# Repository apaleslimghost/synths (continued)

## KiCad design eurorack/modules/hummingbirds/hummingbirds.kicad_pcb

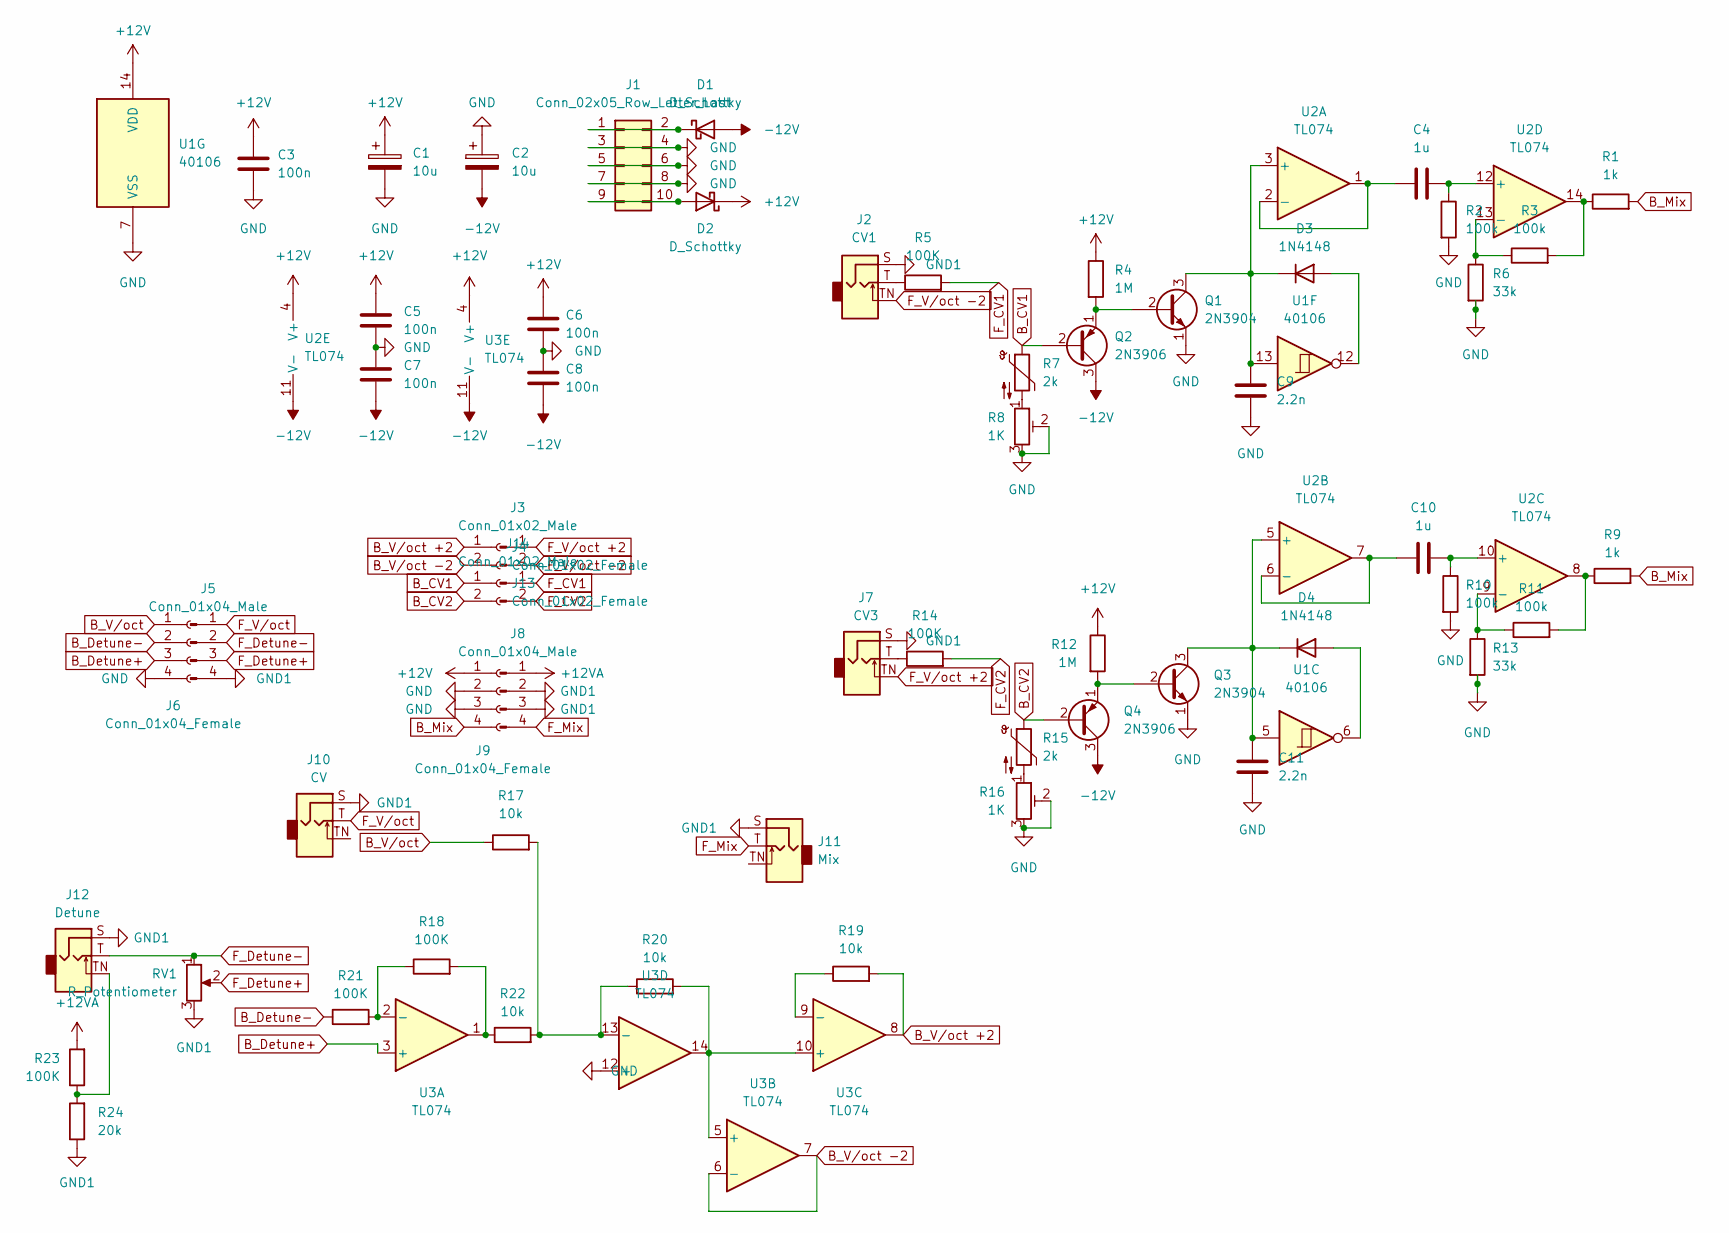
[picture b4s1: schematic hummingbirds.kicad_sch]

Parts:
C1, C2: 10u; CP_Elec_4x5.8
C3, C5, C6, C7, C8: 100n; C_0805_2012Metric_Pad1.18x1.45mm_HandSolder
C4, C10: 1u; C_1210_3225Metric_Pad1.33x2.70mm_HandSolder
C9, C11: 2.2n; C_1206_3216Metric_Pad1.33x1.80mm_HandSolder
D1, D2: D_Schottky; D_SOD-123
D3, D4: 1N4148; D_0805_2012Metric_Pad1.15x1.40mm_HandSolder
J1: Conn_02x05_Row_Letter_Last; PinHeader_2x05_P2.54mm_Vertical_SMD
J2: CV1; Jack_3.5mm_QingPu_WQP-PJ398SM_Vertical
J3, J14: Conn_01x02_Male; PinHeader_1x02_P2.54mm_Vertical
J4, J13: Conn_01x02_Female; PinSocket_1x02_P2.54mm_Vertical
J5, J8: Conn_01x04_Male; PinHeader_1x04_P2.54mm_Vertical
J6, J9: Conn_01x04_Female; PinSocket_1x04_P2.54mm_Vertical
J7: CV3; Jack_3.5mm_QingPu_WQP-PJ398SM_Vertical
J10: CV; Jack_3.5mm_QingPu_WQP-PJ398SM_Vertical
J11: Mix; Jack_3.5mm_QingPu_WQP-PJ398SM_Vertical
J12: Detune; Jack_3.5mm_QingPu_WQP-PJ398SM_Vertical
Q1, Q3: 2N3904; SOT-23_Handsoldering
Q2, Q4: 2N3906; SOT-23_Handsoldering
R1, R9: 1k; R_0805_2012Metric_Pad1.20x1.40mm_HandSolder
R2, R3, R10, R11: 100k; R_0805_2012Metric_Pad1.20x1.40mm_HandSolder
R4, R12: 1M; R_0805_2012Metric_Pad1.20x1.40mm_HandSolder
R5, R14, R18, R21, R23: 100K; R_0805_2012Metric_Pad1.20x1.40mm_HandSolder
R6, R13: 33k; R_0805_2012Metric_Pad1.20x1.40mm_HandSolder
R7, R15: 2k; R_0805_2012Metric_Pad1.20x1.40mm_HandSolder
R8, R16: 1K; Potentiometer_Bourns_3296X_Horizontal
R17, R19, R20, R22: 10k; R_0805_2012Metric_Pad1.20x1.40mm_HandSolder
R24: 20k; R_0805_2012Metric_Pad1.20x1.40mm_HandSolder
RV1: R_Potentiometer; Potentiometer_Alpha_RD901F-40-00D_Single_Vertical
U1: 40106; SOIC-14_3.9x8.7mm_P1.27mm
U2, U3: TL074; SOIC-14_3.9x8.7mm_P1.27mm

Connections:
+12V: C1.1, C3.2, C5.2, C6.2, D2.1 (K), J9.1, R4.1, R12.1, U1.14 (VDD), U2.4 (V+), U3.4 (V+)
+12VA: J8.1, R23.2
-12V: C2.2, C7.1, C8.1, D1.2 (A), Q2.3 (C), Q4.3 (C), U2.11 (V-), U3.11 (V-)
B_CV1: J13.1, Q2.2 (B), R7.1
B_CV2: J13.2, Q4.2 (B), R15.1
B_Detune+: J6.3, U3.3 (+)
B_Detune-: J6.2, R21.1
B_Mix: J9.4, R1.2, R9.2
B_V/oct: J6.1, R17.1
B_V/oct +2: J4.1, R19.2, U3.8
B_V/oct -2: J4.2, U3.6 (-), U3.7
F_CV1: J14.1, R5.2
F_CV2: J14.2, R14.2
F_Detune+: J5.3, RV1.2
F_Detune-: J5.2, J12.T, RV1.1
F_Mix: J8.4, J11.T
F_V/oct: J5.1, J10.T
F_V/oct +2: J3.1, J7.TN
F_V/oct -2: J2.TN, J3.2
GND: C1.2, C2.1, C3.1, C5.1, C6.1, C7.2, C8.2, C9.1, C11.1, J1.3, J1.4, J1.5, J1.6, J1.7, J1.8, J6.4, J9.2, J9.3, Q1.1 (E), Q3.1 (E), R2.2, R6.2, R8.2, R8.3, R10.2, R13.2, R16.2, R16.3, U1.7 (VSS), U3.12 (+)
GND1: J2.S, J5.4, J7.S, J8.2, J8.3, J10.S, J11.S, J12.S, R24.1, RV1.3
unnamed: C4.1, U2.1, U2.2 (-)
unnamed: C4.2, R2.1, U2.12 (+)
unnamed: C9.2, D3.1 (K), Q1.3 (C), U1.13, U2.3 (+)
unnamed: C10.1, U2.6 (-), U2.7
unnamed: C10.2, R10.1, U2.10 (+)
unnamed: C11.2, D4.1 (K), Q3.3 (C), U1.5, U2.5 (+)
unnamed: D1.1 (K), J1.1, J1.2
unnamed: D2.2 (A), J1.9, J1.10
unnamed: D3.2 (A), U1.12
unnamed: D4.2 (A), U1.6
unnamed: J2.T, R5.1
unnamed: J7.T, R14.1
unnamed: J12.TN, R23.1, R24.2
unnamed: Q1.2 (B), Q2.1 (E), R4.2
unnamed: Q3.2 (B), Q4.1 (E), R12.2
unnamed: R1.1, R3.2, U2.14
unnamed: R3.1, R6.1, U2.13 (-)
unnamed: R7.2, R8.1
unnamed: R11.1, R13.1, U2.9 (-)
unnamed: R9.1, R11.2, U2.8
unnamed: R15.2, R16.1
unnamed: R17.2, R20.1, R22.2, U3.13 (-)
unnamed: R18.1, R21.2, U3.2 (-)
unnamed: R18.2, R22.1, U3.1
unnamed: R19.1, U3.9 (-)
unnamed: R20.2, U3.5 (+), U3.10 (+), U3.14

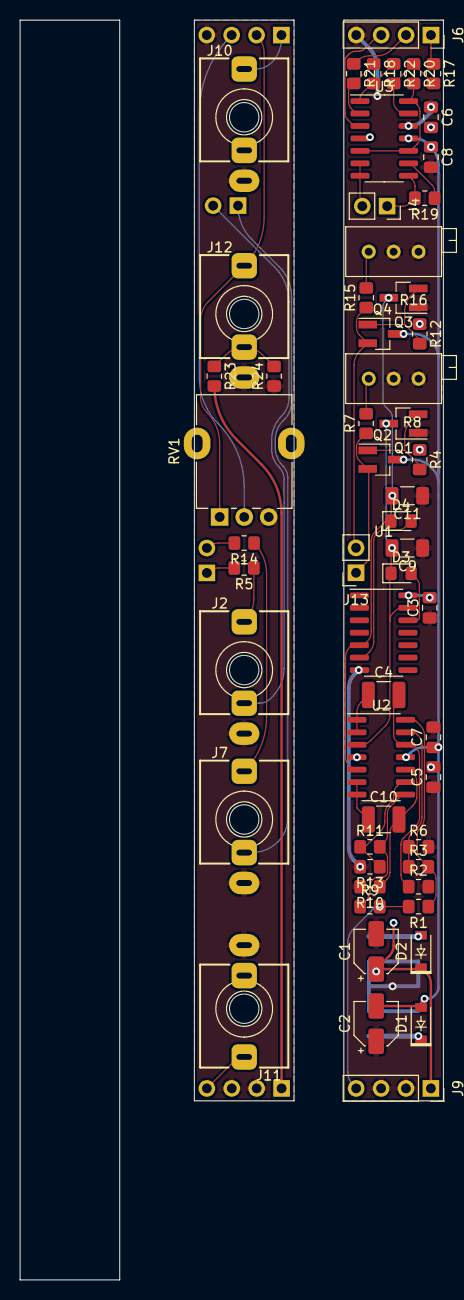
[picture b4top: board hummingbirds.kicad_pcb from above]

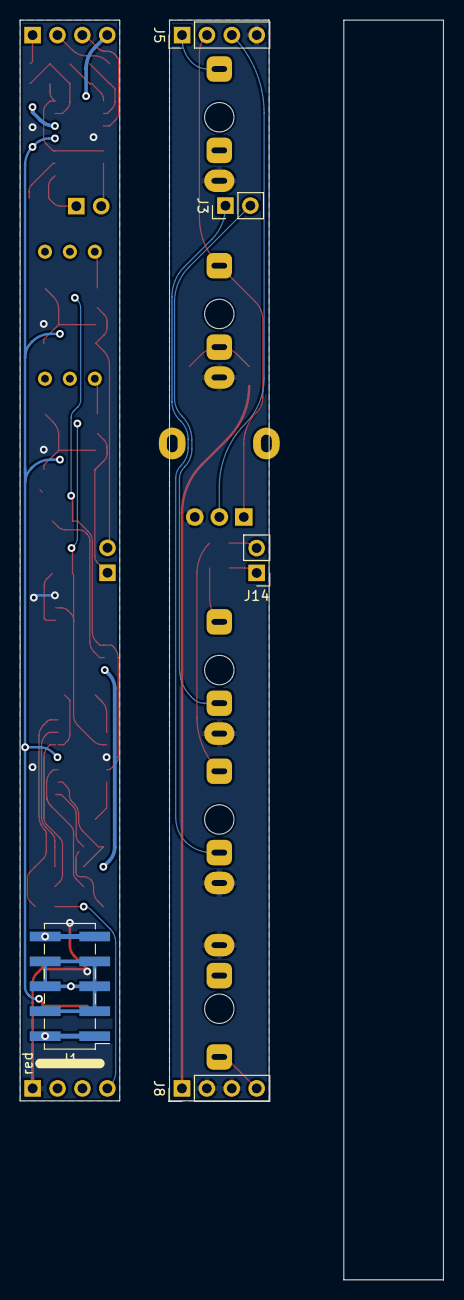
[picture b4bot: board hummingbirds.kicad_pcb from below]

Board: 2 copper layers, 43.2 x 128.5 mm, 61 parts (5 on the bottom side), 47 nets.

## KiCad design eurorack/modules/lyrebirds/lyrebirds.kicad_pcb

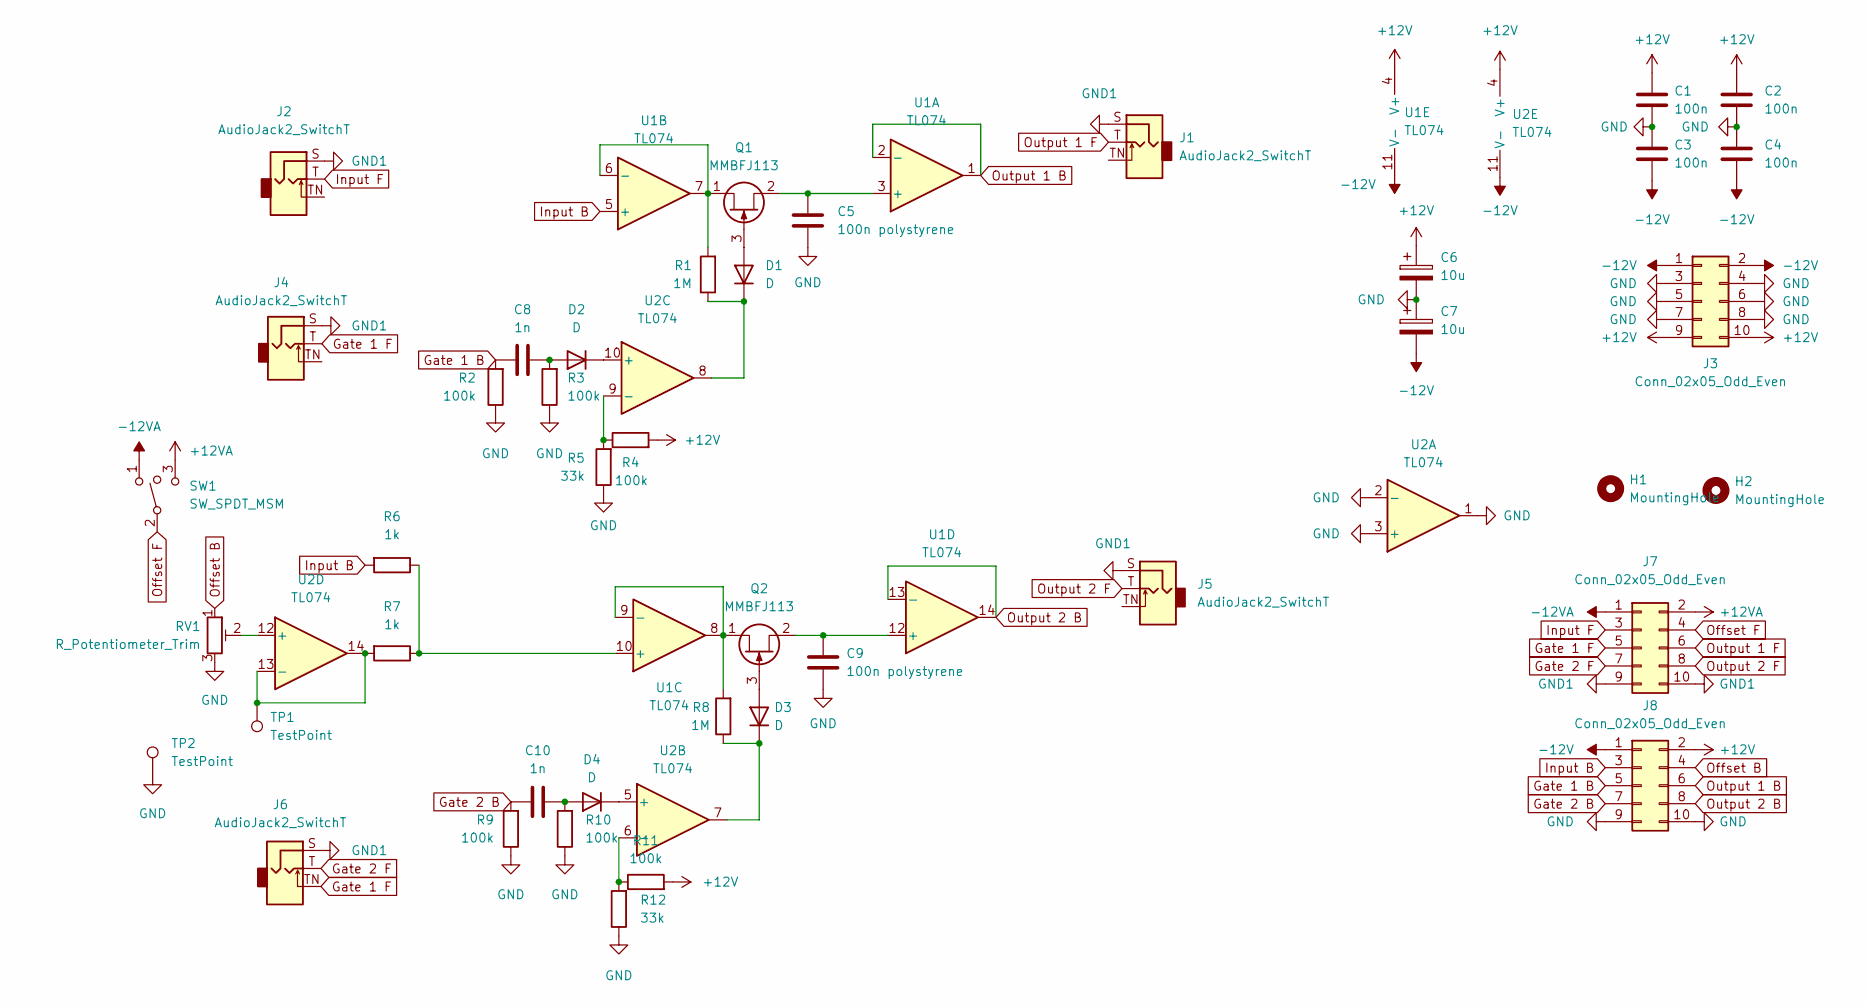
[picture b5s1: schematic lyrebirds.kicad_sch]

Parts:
C1, C2, C3, C4: 100n; C_0805_2012Metric_Pad1.18x1.45mm_HandSolder
C5, C9: 100n polystyrene; C_Rect_L7.2mm_W2.5mm_P5.00mm_FKS2_FKP2_MKS2_MKP2
C6, C7: 10u; CP_EIA-3216-18_Kemet-A_Pad1.58x1.35mm_HandSolder
C8, C10: 1n; C_0805_2012Metric_Pad1.18x1.45mm_HandSolder
D1, D2, D3, D4: D; D_SOD-123
H1, H2: MountingHole; MountingHole_2.2mm_M2
J1, J2, J4, J5, J6: AudioJack2_SwitchT; Jack_3.5mm_QingPu_WQP-PJ301BM_Vertical
J3: Conn_02x05_Odd_Even; PinHeader_2x05_P2.54mm_Vertical_SMD
J7: Conn_02x05_Odd_Even; PinHeader_2x05_P1.00mm_Vertical_SMD
J8: Conn_02x05_Odd_Even; PinSocket_2x05_P1.00mm_Vertical_SMD
Q1, Q2: MMBFJ113; SOT-23
R1, R8: 1M; R_0805_2012Metric_Pad1.20x1.40mm_HandSolder
R2, R3, R4, R9, R10, R11: 100k; R_0805_2012Metric_Pad1.20x1.40mm_HandSolder
R5, R12: 33k; R_0805_2012Metric_Pad1.20x1.40mm_HandSolder
R6, R7: 1k; R_0805_2012Metric_Pad1.20x1.40mm_HandSolder
RV1: R_Potentiometer_Trim; Potentiometer_Bourns_3296W_Vertical
SW1: SW_SPDT_MSM; Sub Mini Toggle Switch SPDT
TP1, TP2: TestPoint; TestPoint_Pad_D1.5mm
U1, U2: TL074; SOIC-14_3.9x8.7mm_P1.27mm

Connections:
+12V: C1.1, C2.1, C6.1, J3.9, J3.10, J8.2, R4.2, R11.2, U1.4 (V+), U2.4 (V+)
+12VA: J7.2, SW1.3
-12V: C3.2, C4.2, C7.2, J3.1, J3.2, J8.1, U1.11 (V-), U2.11 (V-)
-12VA: J7.1, SW1.1
GND: C1.2, C2.2, C3.1, C4.1, C5.2, C6.2, C7.1, C9.2, J3.3, J3.4, J3.5, J3.6, J3.7, J3.8, J8.9, J8.10, R2.1, R3.1, R5.1, R9.1, R10.1, R12.1, RV1.3, TP2.1, U2.1, U2.2 (-), U2.3 (+)
GND1: J1.S, J2.S, J4.S, J5.S, J6.S, J7.9, J7.10
Gate 1 B: C8.1, J8.5, R2.2
Gate 1 F: J4.T, J6.TN, J7.5
Gate 2 B: C10.1, J8.7, R9.2
Gate 2 F: J6.T, J7.7
Input B: J8.3, R6.2, U1.5 (+)
Input F: J2.T, J7.3
unnamed: C5.1, Q1.2 (S), U1.3 (+)
unnamed: C8.2, D2.2 (A), R3.2
unnamed: C9.1, Q2.2 (S), U1.12 (+)
unnamed: C10.2, D4.2 (A), R10.2
unnamed: D1.1 (K), R1.1, U2.8
unnamed: D1.2 (A), Q1.3 (G)
unnamed: D2.1 (K), U2.10 (+)
unnamed: D3.1 (K), R8.1, U2.7
unnamed: D3.2 (A), Q2.3 (G)
unnamed: D4.1 (K), U2.5 (+)
unnamed: Q1.1 (D), R1.2, U1.6 (-), U1.7
unnamed: Q2.1 (D), R8.2, U1.8, U1.9 (-)
unnamed: R4.1, R5.2, U2.9 (-)
unnamed: R6.1, R7.1, U1.10 (+)
unnamed: R7.2, TP1.1, U2.13 (-), U2.14
unnamed: R11.1, R12.2, U2.6 (-)
unnamed: RV1.2, U2.12 (+)
Offset B: J8.4, RV1.1
Offset F: J7.4, SW1.2
Output 1 B: J8.6, U1.1, U1.2 (-)
Output 1 F: J1.T, J7.6
Output 2 B: J8.8, U1.13 (-), U1.14
Output 2 F: J5.T, J7.8

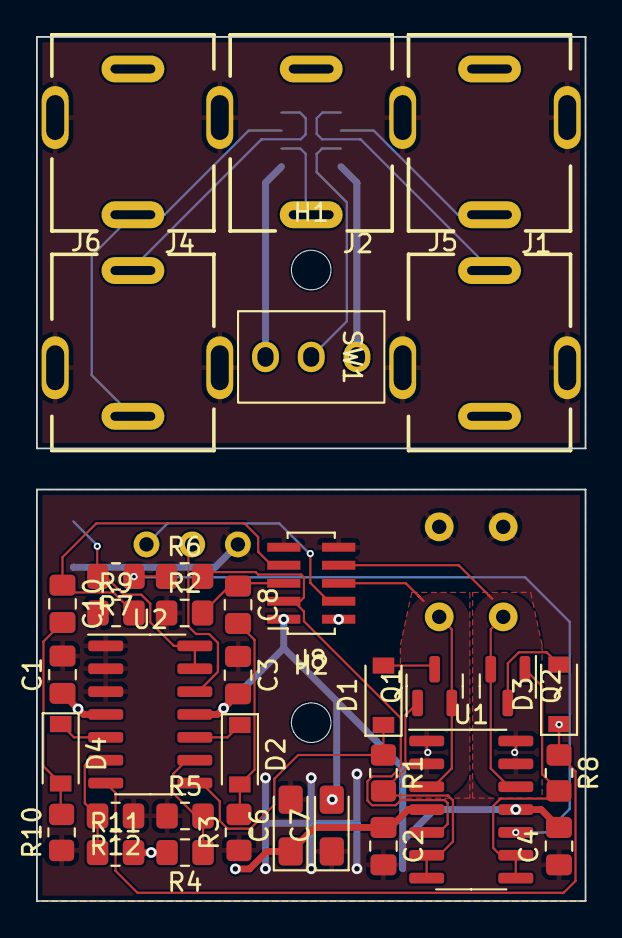
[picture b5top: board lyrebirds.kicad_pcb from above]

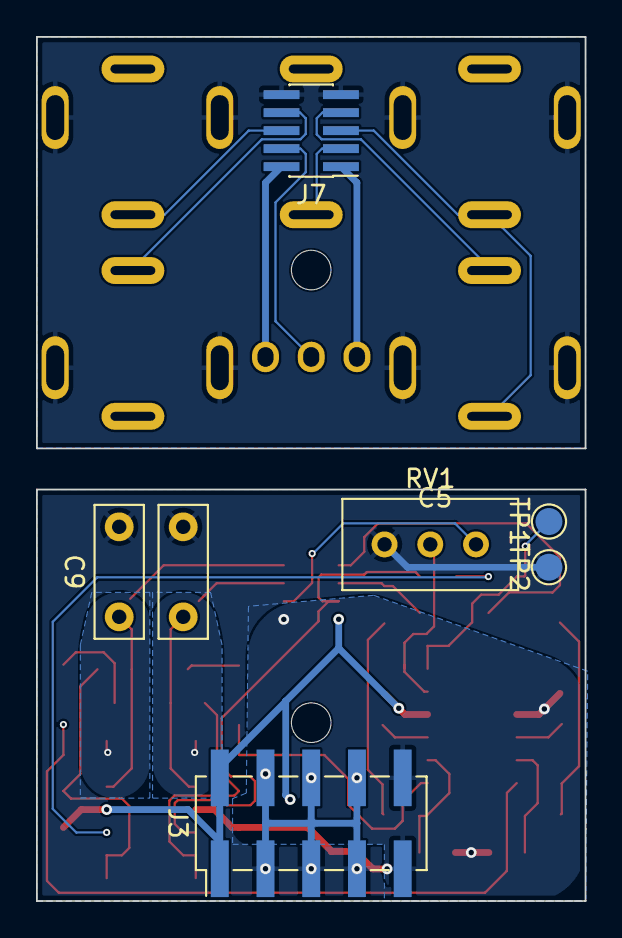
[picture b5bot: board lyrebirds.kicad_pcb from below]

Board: 2 copper layers, 30.5 x 48.0 mm, 44 parts (7 on the bottom side), 35 nets.

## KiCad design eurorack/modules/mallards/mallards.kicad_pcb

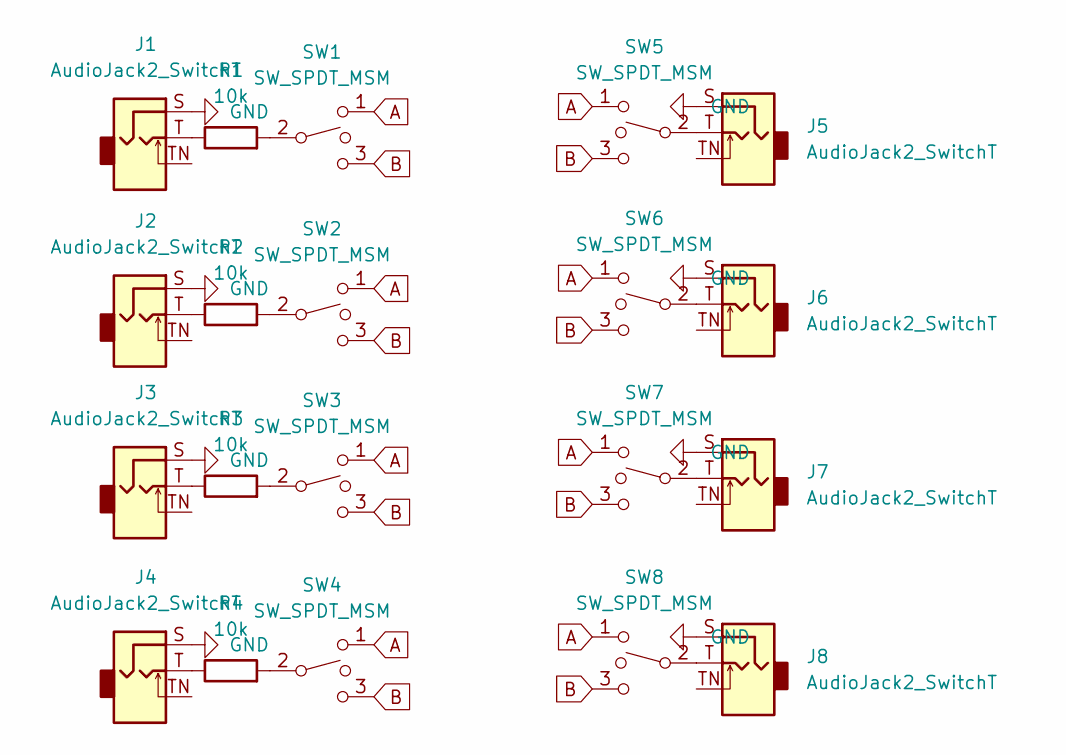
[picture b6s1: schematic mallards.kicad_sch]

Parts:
J1, J2, J3, J4, J5, J6, J7, J8: AudioJack2_SwitchT; Jack_3.5mm_QingPu_WQP-PJ398SM_Vertical
R1, R2, R3, R4: 10k; R_Axial_DIN0207_L6.3mm_D2.5mm_P7.62mm_Horizontal
SW1, SW2, SW3, SW4, SW5, SW6, SW7, SW8: SW_SPDT_MSM; Sub Mini Toggle Switch SPDT

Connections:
A: SW1.1, SW2.1, SW3.1, SW4.1, SW5.1, SW6.1, SW7.1, SW8.1
B: SW1.3, SW2.3, SW3.3, SW4.3, SW5.3, SW6.3, SW7.3, SW8.3
GND: J1.S, J2.S, J3.S, J4.S, J5.S, J6.S, J7.S, J8.S
unnamed: J1.T, R1.1
unnamed: J2.T, R2.1
unnamed: J3.T, R3.1
unnamed: J4.T, R4.1
unnamed: J5.T, SW5.2
unnamed: J6.T, SW6.2
unnamed: J7.T, SW7.2
unnamed: J8.T, SW8.2
unnamed: R1.2, SW1.2
unnamed: R2.2, SW2.2
unnamed: R3.2, SW3.2
unnamed: R4.2, SW4.2

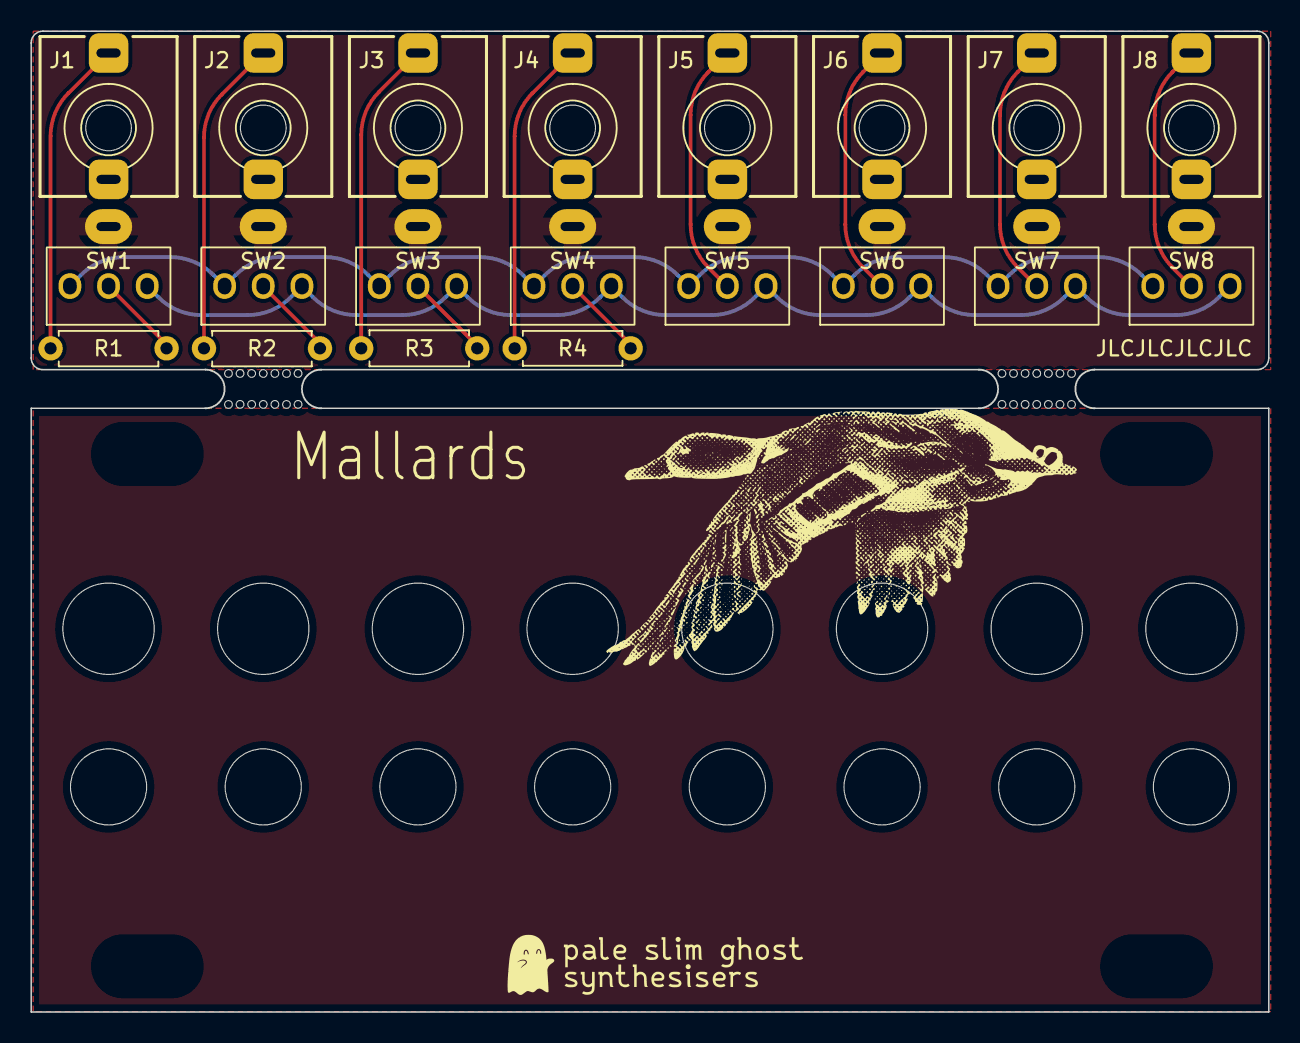
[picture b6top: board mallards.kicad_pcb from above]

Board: 2 copper layers, 81.3 x 64.4 mm, 22 parts (0 on the bottom side), 15 nets.

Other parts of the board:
mouse-bite-2mm-slot, mouse-bite-2mm-slot#2: VAL**; mousebite-2.54x5.08mm

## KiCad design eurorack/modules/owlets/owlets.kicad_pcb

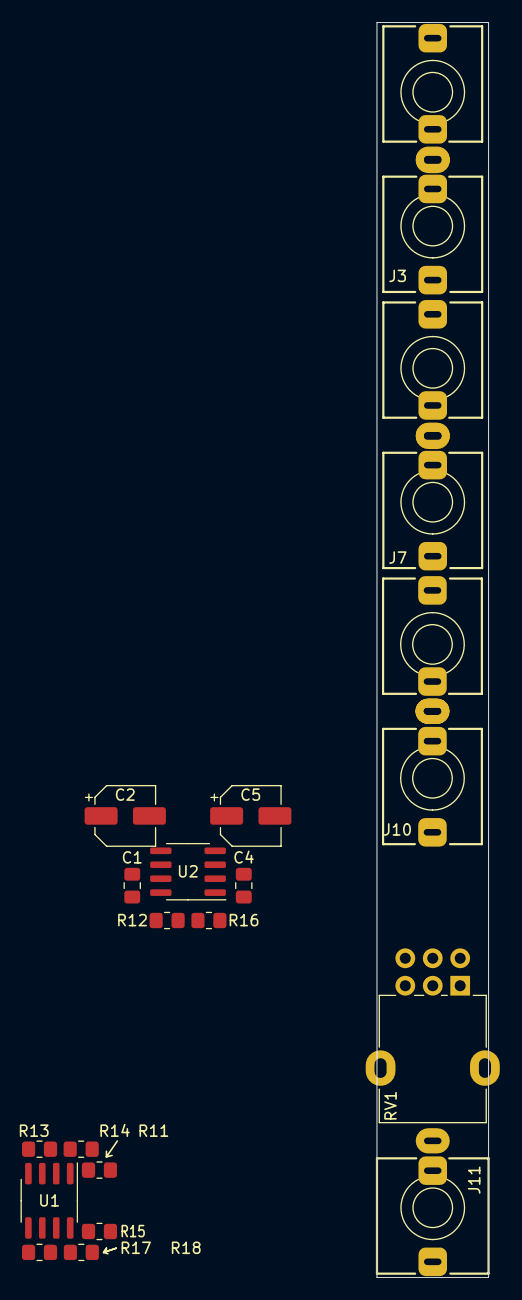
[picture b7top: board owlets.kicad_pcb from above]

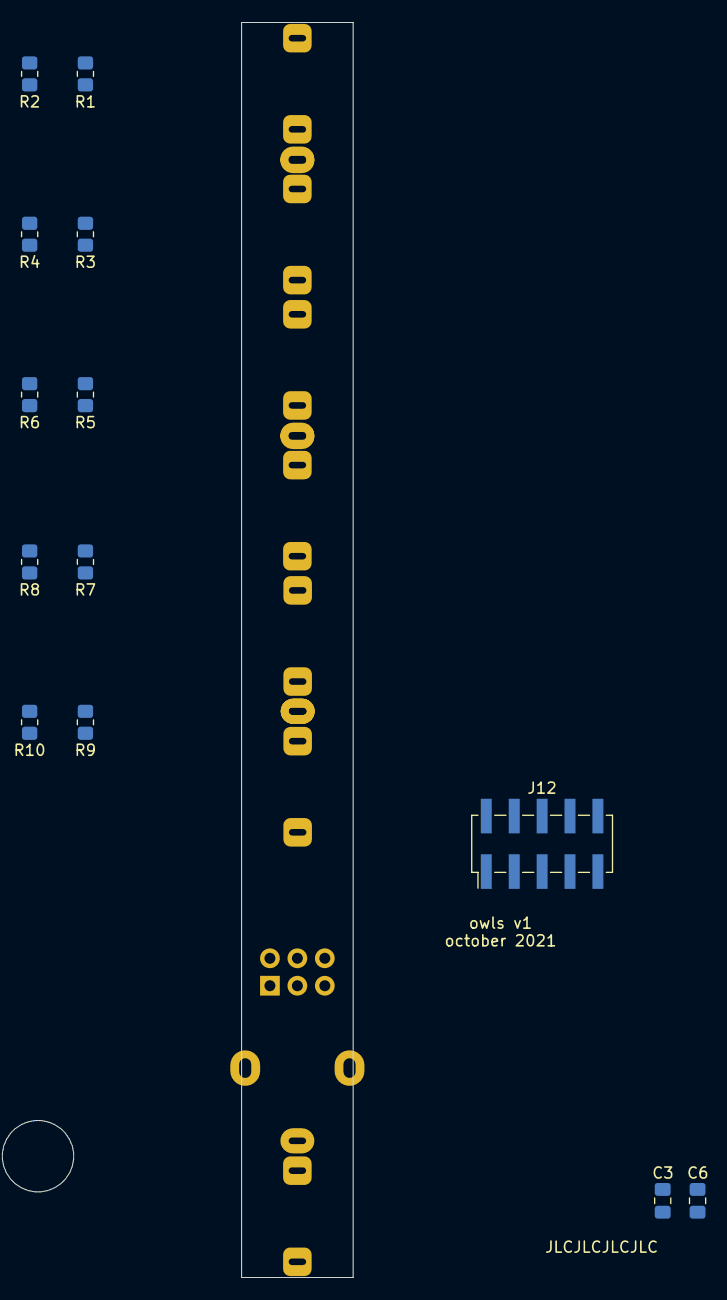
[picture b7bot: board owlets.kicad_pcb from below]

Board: 2 copper layers, 10.2 x 114.3 mm, 35 parts (13 on the bottom side), 21 nets, no tracks yet.

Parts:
C1, C3, C4, C6: C; C_0805_2012Metric_Pad1.18x1.45mm_HandSolder
C2, C5: C_Polarized; CP_Elec_5x4.5
J1, J3, J5, J7, J9, J10: AudioJack2_SwitchT; Jack_3.5mm_QingPu_WQP-PJ398SM_Vertical
J11: AudioJack3; Jack_3.5mm_QingPu_WQP-PJ366ST_Vertical
J12: Conn_02x05_Odd_Even; PinHeader_2x05_P2.54mm_Vertical_SMD
R1, R2, R3, R4, R5, R6, R7, R8, R9, R10, R12, R16: 10k; R_0805_2012Metric_Pad1.20x1.40mm_HandSolder
R11, R15: 47r; R_0805_2012Metric_Pad1.20x1.40mm_HandSolder
R13, R14, R17, R18: 2k; R_0805_2012Metric_Pad1.20x1.40mm_HandSolder
RV1: R_Potentiometer_Dual; Potentiometer_Alpha_RD902F-40-00D_Dual_Vertical
U1: OPA2134; SOIC-8_3.9x4.9mm_P1.27mm
U2: NE5532; SOIC-8_3.9x4.9mm_P1.27mm

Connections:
+12V: C1.1, C2.1, C3.1, J12.9, J12.10, U1.8 (V+), U2.8 (V+)
-12V: C4.2, C5.2, C6.2, J12.1, J12.2, U1.4 (V-), U2.4 (V-)
GND: C1.2, C2.2, C3.2, C4.1, C5.1, C6.1, J1.S, J3.S, J5.S, J7.S, J9.S, J10.S, J11.S, J12.3, J12.4, J12.5, J12.6, J12.7, J12.8, R13.1, R17.1, RV1.1, RV1.4, U2.3 (+), U2.5 (+)
L: R1.2, R3.2, R5.2, R7.2, R9.2, R12.1, U2.6 (-)
unnamed: J1.T, R1.1
unnamed: J3.T, R3.1
unnamed: J5.T, R5.1
unnamed: J7.T, R7.1
unnamed: J10.T, R10.1
unnamed: J9.T, J10.TN, R9.1
unnamed: J11.R, R15.2
unnamed: J11.T, R11.2
unnamed: R11.1, R14.2, U1.1
unnamed: R12.2, RV1.3, U2.7
unnamed: R13.2, R14.1, U1.2 (-)
unnamed: R15.1, R18.2, U1.7
unnamed: R16.2, RV1.6, U2.1
unnamed: R17.2, R18.1, U1.6 (-)
unnamed: RV1.2, U1.3 (+)
unnamed: RV1.5, U1.5 (+)
R: R2.2, R4.2, R6.2, R8.2, R10.2, R16.1, U2.2 (-)
